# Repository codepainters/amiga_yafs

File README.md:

# Yet Another FDD Swapper for Amiga 500

This is my project of Amiga FDD swapper, based on `ATtiny 404` MCU. 

## What it does?

It allows for swapping internal `DF0:` drive and `DF1:` external drive (by crossing `SEL0` and `SEL1` signals from `MOS 8520 EVEN CIA`). Holding `Ctrl - Amiga - Amiga` keys for at least 2 seconds switches between normal / swapped configurations. The last used configuration is automatically restored on power up (unless configured not to do so, see below). Switching is confirmed with 1 (for normal) or 2 (for swapped) beeps.

The project consists of 2 separate PCBs:

* a bigger one that goes under the `EVEN CIA` chip - responsible for `SEL0` / `SEL1` swapping.
* a smaller one that which goes between Amiga motherboard and floppy ribbon cable. This PCB allows for internal FDD to be detected as DF1 (it's optional).

This is how the boards look like assembled in my Amiga 500 Rev 6A.

## Why another one?

Well, there are many FDD swapper projects already, all of these mods basically swap `SEL0` and `SEL1` of the `Even CIA`, using anything from simple mechanical switch to `74LS153` multiplexer (or even `4066` CMOS analog switch) driven by `ATtiny` MCU. Please note, that swapping `SEL0/1` signals is not enough for internal drive to work as `DF1:`, additional circuitry is needed to drive `~RDY` signal during the drive enumeration at boot time.

Looking for a solution, I've found [Amiga Floppy Swap](https://github.com/retronicdesign/AmigaFloppySwap) project, which is almost exactly what I need. However, I decided to make it slightly simpler:

* my project uses only a single chip, `ATtiny 404` microcontroller, which costs below **0.50 EUR** (at least at the time of this writing),
* the smaller board (which allows for internal drive being enumerated as `DF1:`) doesn't need to be connected with the bigger board. Actually it contains only 2 MOSFETs and 2 resistors and doesn't need any extra connections, beside the floppy flat cable (not even +5V supply!). 
* it is configurable - one can chose if it beeps on every start (or only when changing the configuration) and which configuration (last used vs always swapped vs always straight) it should use upon powering up (see [pcb_cia](pcb_cia) description for details).
* the smaller board is plugged into the mainboard (as opposed to between the cable and FDD) - this way possible collision with the EMI shielding sheet metal is entirely avoided.

Also, it's fun to make something new (even if reinventing the wheel).

## Project files

This repository contains 3 main directories (look there for more details, assembly instructions, etc.):

* [pcb_cia](pcb_cia) - KiCAD project of the bigger PCB which goes under the `CIA` chip.
* [pcb_df1](pcb_df1) - KiCAD project of the smaller PCB which goes between Amiga motherboard and the FDD ribbon cable. 

* [firmware](firmware) for the `ATtiny 404` MCU on the `pcb_cia` board (including programming instructions).

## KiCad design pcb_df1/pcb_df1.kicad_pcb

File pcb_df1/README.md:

# DF1 board

Note: this is the PCB rendered from the bottom side.

* [schematics in PDF format](pcb_df1.pdf)
* [Gerbers and Excellon](production/pcb_df1.zip)
* [BOM](production/bom.csv)

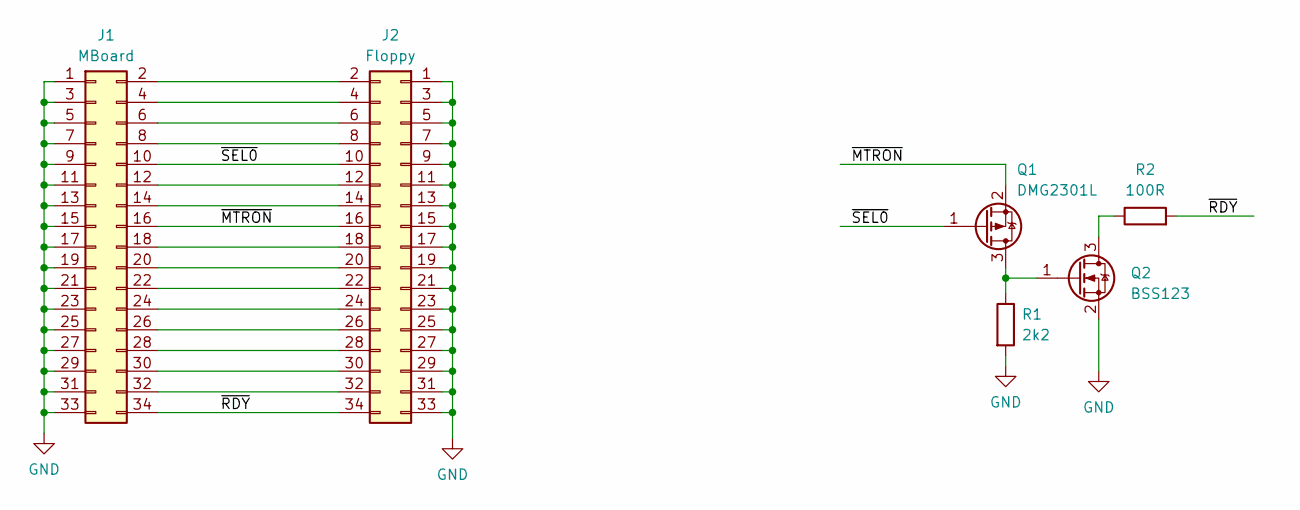
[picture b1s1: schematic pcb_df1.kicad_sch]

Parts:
J1: MBoard; PinSocket_2x17_P2.54mm_Vertical
J2: Floppy; PinHeader_2x17_P2.54mm_Vertical
Q1: DMG2301L; SOT-23
Q2: BSS123; SOT-23
R1: 2k2; R_0805_2012Metric_Pad1.20x1.40mm_HandSolder
R2: 100R; R_0805_2012Metric_Pad1.20x1.40mm_HandSolder

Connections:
/~MTRON: J1.16, J2.16, Q1.2 (S)
/~RDY: J1.34, J2.34, R2.2
/~SEL0: J1.10, J2.10, Q1.1 (G)
GND: J1.1, J1.3, J1.5, J1.7, J1.9, J1.11, J1.13, J1.15, J1.17, J1.19, J1.21, J1.23, J1.25, J1.27, J1.29, J1.31, J1.33, J2.1, J2.3, J2.5, J2.7, J2.9, J2.11, J2.13, J2.15, J2.17, J2.19, J2.21, J2.23, J2.25, J2.27, J2.29, J2.31, J2.33, Q2.2 (S), R1.2
unnamed: J1.2, J2.2
unnamed: J1.4, J2.4
unnamed: J1.6, J2.6
unnamed: J1.8, J2.8
unnamed: J1.12, J2.12
unnamed: J1.14, J2.14
unnamed: J1.18, J2.18
unnamed: J1.20, J2.20
unnamed: J1.22, J2.22
unnamed: J1.24, J2.24
unnamed: J1.26, J2.26
unnamed: J1.28, J2.28
unnamed: J1.30, J2.30
unnamed: J1.32, J2.32
unnamed: Q1.3 (D), Q2.1 (G), R1.1
unnamed: Q2.3 (D), R2.1

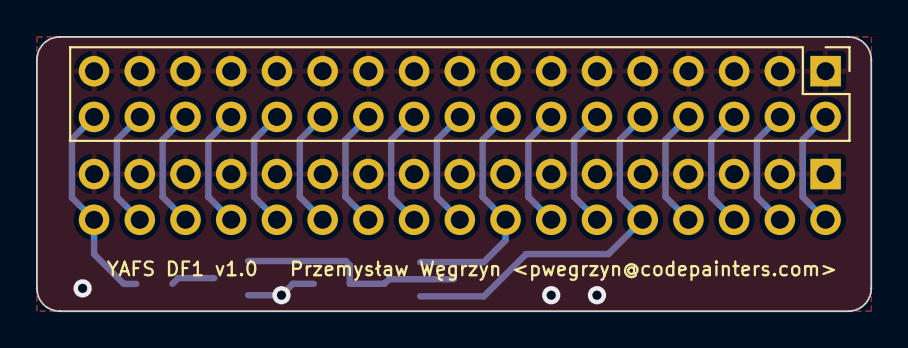
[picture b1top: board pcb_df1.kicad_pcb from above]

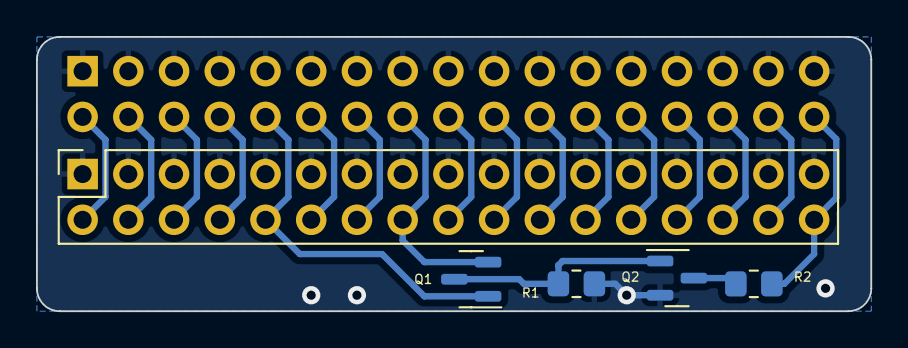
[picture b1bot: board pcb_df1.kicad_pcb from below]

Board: 2 copper layers, 46.4 x 15.2 mm, 6 parts (5 on the bottom side), 20 nets.

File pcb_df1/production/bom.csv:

Designator,Footprint,Quantity,Value,LCSC Part #
J1,PinSocket_2x17_P2.54mm_Vertical,1,MBoard,
J2,PinHeader_2x17_P2.54mm_Vertical,1,Floppy,
Q1,SOT-23,1,DMG2301L,
Q2,SOT-23,1,BSS123,
R1,0805,1,2k2,
R2,0805,1,100R,

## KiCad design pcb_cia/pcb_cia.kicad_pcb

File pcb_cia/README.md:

# CIA board

* [schematics in PDF format](pcb_cia.pdf)
* [Gerbers and Excellon](production/pcb_cia.zip)
* [BOM](production/bom.csv)

Note:

* for `BZ1` buzzer I have used `KPM1201A` magnetic buzzer, but pretty much anything should work, as long as U1 maximum output current (20 mA) is not exceeded. You may need to adjust R1 value.
* I've added `D1` diode as a back EMF protection, but it turned out it is not really necessary with the buzzer I use. 
* for programming instructions, see [here](../firmware)

## Configuration

The J3, J4 and J5 solder bridge jumpers can be used to configure the device:

* if `J3` is open, the buzzer beeps only to confirm the mode changing, if `J3` is closed the buzzer beeps (once or twice) at each power-up, to remind what mode is currently selected.
* if `J4` is open, last used mode is restored on power-up. If it is closed, the same mode is selected at each power-up - swapped (if `J5` is open) or normal (if `J5` is closed). If `J4` is open, `J5` state is ignored.

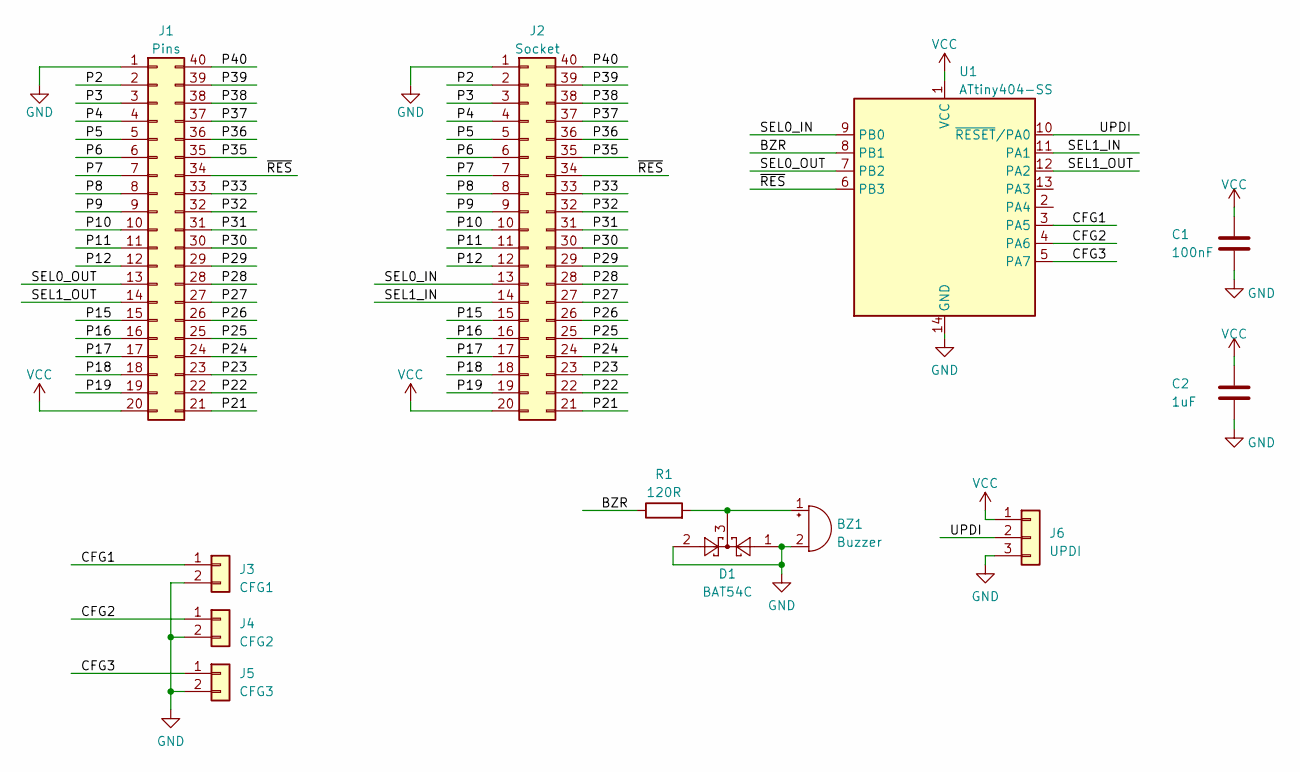
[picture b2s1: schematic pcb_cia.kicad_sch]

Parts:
BZ1: Buzzer; buzzer
C1: 100nF; C_0603_1608Metric_Pad1.08x0.95mm_HandSolder
C2: 1uF; C_1206_3216Metric_Pad1.33x1.80mm_HandSolder
D1: BAT54C; SOT-23
J1: Pins; DIP-40_W15.24mm
J2: Socket; DIP-40_W15.24mm_Socket
J3: CFG1; SolderJumper-2_P1.3mm_Open_TrianglePad1.0x1.5mm
J4: CFG2; SolderJumper-2_P1.3mm_Open_TrianglePad1.0x1.5mm
J5: CFG3; SolderJumper-2_P1.3mm_Open_TrianglePad1.0x1.5mm
J6: UPDI; PinHeader_1x03_P2.54mm_Vertical
R1: 120R; R_0603_1608Metric
U1: ATtiny404-SS; SOIC-14_3.9x8.7mm_P1.27mm

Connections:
/BZR: R1.1, U1.8 (PB1)
/CFG1: J3.1, U1.3 (PA5)
/CFG2: J4.1, U1.4 (PA6)
/CFG3: J5.1, U1.5 (PA7)
/P2: J1.2, J2.2
/P3: J1.3, J2.3
/P4: J1.4, J2.4
/P5: J1.5, J2.5
/P6: J1.6, J2.6
/P7: J1.7, J2.7
/P8: J1.8, J2.8
/P9: J1.9, J2.9
/P10: J1.10, J2.10
/P11: J1.11, J2.11
/P12: J1.12, J2.12
/P15: J1.15, J2.15
/P16: J1.16, J2.16
/P17: J1.17, J2.17
/P18: J1.18, J2.18
/P19: J1.19, J2.19
/P21: J1.21, J2.21
/P22: J1.22, J2.22
/P23: J1.23, J2.23
/P24: J1.24, J2.24
/P25: J1.25, J2.25
/P26: J1.26, J2.26
/P27: J1.27, J2.27
/P28: J1.28, J2.28
/P29: J1.29, J2.29
/P30: J1.30, J2.30
/P31: J1.31, J2.31
/P32: J1.32, J2.32
/P33: J1.33, J2.33
/P35: J1.35, J2.35
/P36: J1.36, J2.36
/P37: J1.37, J2.37
/P38: J1.38, J2.38
/P39: J1.39, J2.39
/P40: J1.40, J2.40
/SEL0_IN: J2.13, U1.9 (PB0)
/SEL0_OUT: J1.13, U1.7 (PB2)
/SEL1_IN: J2.14, U1.11 (PA1)
/SEL1_OUT: J1.14, U1.12 (PA2)
/UPDI: J6.2, U1.10 (~RESET/PA0)
/~RES: J1.34, J2.34, U1.6 (PB3)
GND: BZ1.2 (+), C1.2, C2.2, D1.1, D1.2, J1.1, J2.1, J3.2, J4.2, J5.2, J6.3, U1.14 (GND)
unnamed: BZ1.1 (-), D1.3, R1.2
VCC: C1.1, C2.1, J1.20, J2.20, J6.1, U1.1 (VCC)

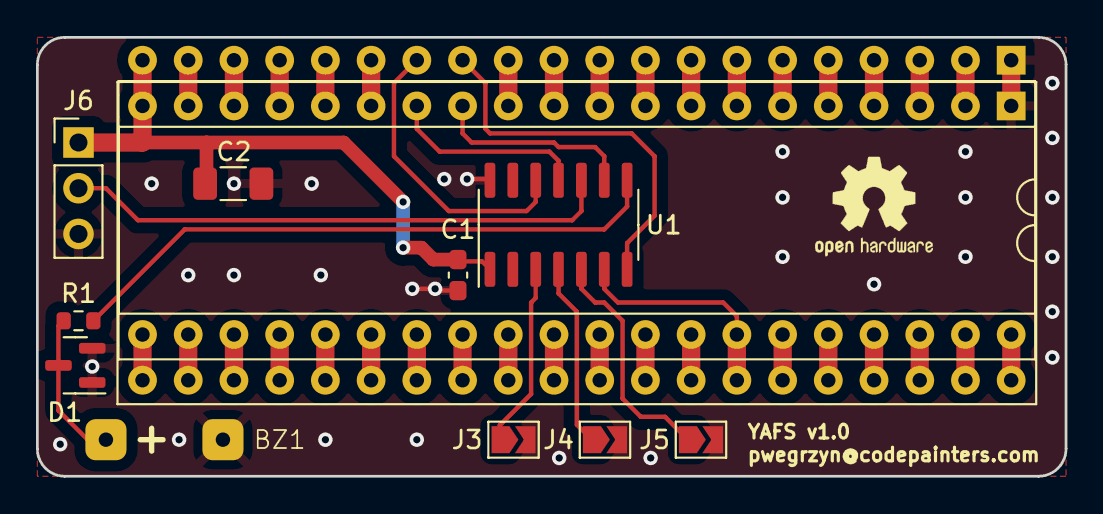
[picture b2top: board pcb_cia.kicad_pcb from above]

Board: 2 copper layers, 57.1 x 24.4 mm, 12 parts (0 on the bottom side), 48 nets.

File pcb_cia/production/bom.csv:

Designator,Footprint,Quantity,Value,LCSC Part #
BZ1,buzzer,1,Buzzer,
C1,0603,1,100nF,
C2,1206,1,1uF,
D1,SOT-23,1,BAT54C,
J1,DIP-40_W15.24mm,1,Pins,
J2,DIP-40_W15.24mm_Socket,1,Socket,
J3,SolderJumper-2_P1.3mm_Open_TrianglePad1.0x1.5mm,1,CFG1,
J4,SolderJumper-2_P1.3mm_Open_TrianglePad1.0x1.5mm,1,CFG2,
J5,SolderJumper-2_P1.3mm_Open_TrianglePad1.0x1.5mm,1,CFG3,
J6,PinHeader_1x03_P2.54mm_Vertical,1,UPDI,
R1,0603,1,120R,
U1,SOIC-14_3.9x8.7mm_P1.27mm,1,ATtiny404-SS,

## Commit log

2023-10-27 DF1 poroject bootstrapped
2023-10-31 CIA PCB completed
2023-11-02 DF1 (floppy detection) PCB completed.
2023-11-02 PCB DF1: slightly bigger vias
2023-11-02 Compined PCB ready for ordering.
    gerberes.zip can be uploaded directly to JLCPCB.
2023-11-02 Combined PCB - snap-off tabs widened to 120 mils.
2023-11-02 pcb_df1: changed orinetation
2023-11-02 Combined PCB: redone to fix silk screen labels orientation
2023-11-02 Combined PCB - larger slot, as per JLCPCB request.
2023-11-09 Initial makefile
2023-11-09 Sleep CPU between interrupts. Simplify buzzer control.
2023-11-09 Firmware cleanup.
2023-11-10 Firmware README
2023-11-13 Initial firmware.
2023-11-13 git-ignore CLion files
2023-11-27 DF1 board reworked
    New version sits on the other end of the flat cable.
2023-11-28 Dropping combined board, JLC doesn't like it ;)
2023-11-28 DF1: GND fills reworked
2023-12-03 Added production output for DF1 board (gerbers, BOM, etc.)
2023-12-03 Main README file.
2023-12-04 Firware README updated.
2024-01-05 DF1: R1 value fixed
2024-01-05 pcb_df1: updated production files
2024-01-05 pcb_df1: added schematic PDF
2024-01-05 pcb_cia: gerbers
2024-01-05 Top-level README updated
2024-01-05 Minor README update.
2024-01-05 pcb_df1: README file
2024-01-05 CIA: README added
2024-01-05 pcb_cia schematics as PDF
2024-01-05 Firmware: fix README path
2024-01-06 Updated README for CIA PCB (configuration).
2024-01-06 Minor README fix.
